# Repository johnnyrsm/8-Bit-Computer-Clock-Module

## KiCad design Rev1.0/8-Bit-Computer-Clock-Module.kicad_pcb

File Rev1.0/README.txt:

//----------------------------------
//      Credits
//----------------------------------

Original Design/Idea by Ben Eater: https://eater.net/

Be sure to check out Ben Eater's home page and youtube channel to check out some more cool stuff.

//----------------------------------
//      General Description
//----------------------------------

Talk about astable, monostable and bistable configs, explain differences and
explain the functionality of the circuit as a whole i.e. generating a continuous clock
or step by step mode using the push button.

Simple PCB layout to practice, made for fun/practice.

Any comments/feedback welcome.

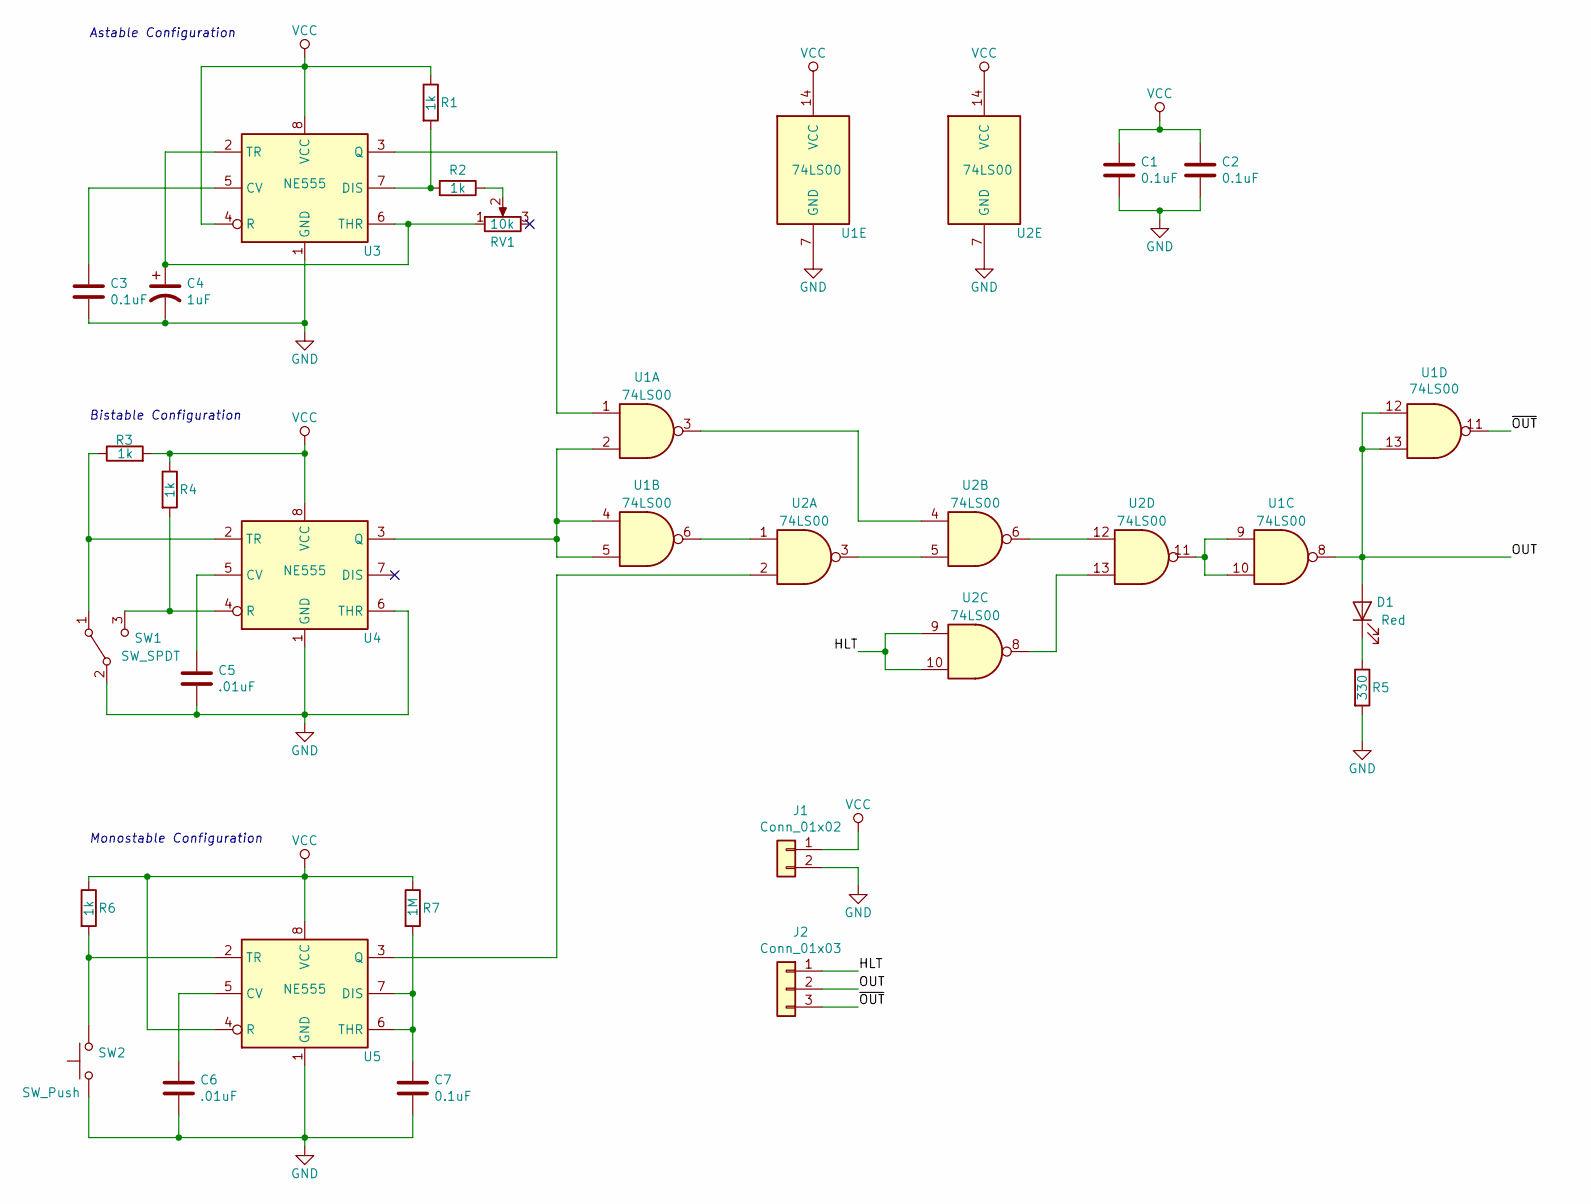
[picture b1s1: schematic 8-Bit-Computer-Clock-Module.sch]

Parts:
C1, C2, C3, C7: 0.1uF; C_Rect_L4.0mm_W2.5mm_P2.50mm
C4: 1uF; CP_Radial_D5.0mm_P2.50mm
C5, C6: .01uF; C_Rect_L4.0mm_W2.5mm_P2.50mm
D1: Red; LED_D3.0mm
J1: Conn_01x02; Pin_Header_Straight_1x02_Pitch2.54mm
J2: Conn_01x03; Pin_Header_Straight_1x03_Pitch2.54mm
R1, R2, R3, R4, R6: 1k; R_Axial_DIN0207_L6.3mm_D2.5mm_P7.62mm_Horizontal
R5: 330; R_Axial_DIN0207_L6.3mm_D2.5mm_P7.62mm_Horizontal
R7: 1M; R_Axial_DIN0207_L6.3mm_D2.5mm_P7.62mm_Horizontal
RV1: 10k; Trimpot_Bourns_3386
SW1: SW_SPDT; Min_Slide_Switch_OS_SPDT
SW2: SW_Push; Sw_Tactile_THT_2_Pin
U1, U2: 74LS00; DIP-14_W7.62mm_Socket
U3, U4, U5: NE555; DIP-8_W7.62mm_Socket

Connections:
/HLT: J2.1, U2.9, U2.10
/OUT: D1.2 (A), J2.2, U1.8, U1.12, U1.13
/~OUT: J2.3, U1.11
GND: C1.2, C2.2, C3.2, C4.2, C5.2, C6.2, C7.2, J1.2, R5.2, SW1.2 (B), SW2.1, U1.7 (GND), U2.7 (GND), U3.1 (GND), U4.1 (GND), U4.6 (THR), U5.1 (GND)
unnamed: C3.1, U3.5 (CV)
unnamed: C4.1, RV1.1, U3.2 (TR), U3.6 (THR)
unnamed: C5.1, U4.5 (CV)
unnamed: C6.1, U5.5 (CV)
unnamed: C7.1, R7.2, U5.6 (THR), U5.7 (DIS)
unnamed: D1.1 (K), R5.1
unnamed: R1.2, R2.2, U3.7 (DIS)
unnamed: R2.1, RV1.2
unnamed: R3.1, SW1.1 (A), U4.2 (TR)
unnamed: R4.2, SW1.3 (C), U4.4 (R)
unnamed: R6.2, SW2.2, U5.2 (TR)
unnamed: U1.1, U3.3 (Q)
unnamed: U1.2, U1.4, U1.5, U4.3 (Q)
unnamed: U1.3, U2.4
unnamed: U1.6, U2.1
unnamed: U1.9, U1.10, U2.11
unnamed: U2.2, U5.3 (Q)
unnamed: U2.3, U2.5
unnamed: U2.6, U2.12
unnamed: U2.8, U2.13
VCC: C1.1, C2.1, J1.1, R1.1, R3.2, R4.1, R6.1, R7.1, U1.14 (VCC), U2.14 (VCC), U3.4 (R), U3.8 (VCC), U4.8 (VCC), U5.4 (R), U5.8 (VCC)

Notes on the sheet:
Astable Configuration
Bistable Configuration
Monostable Configuration

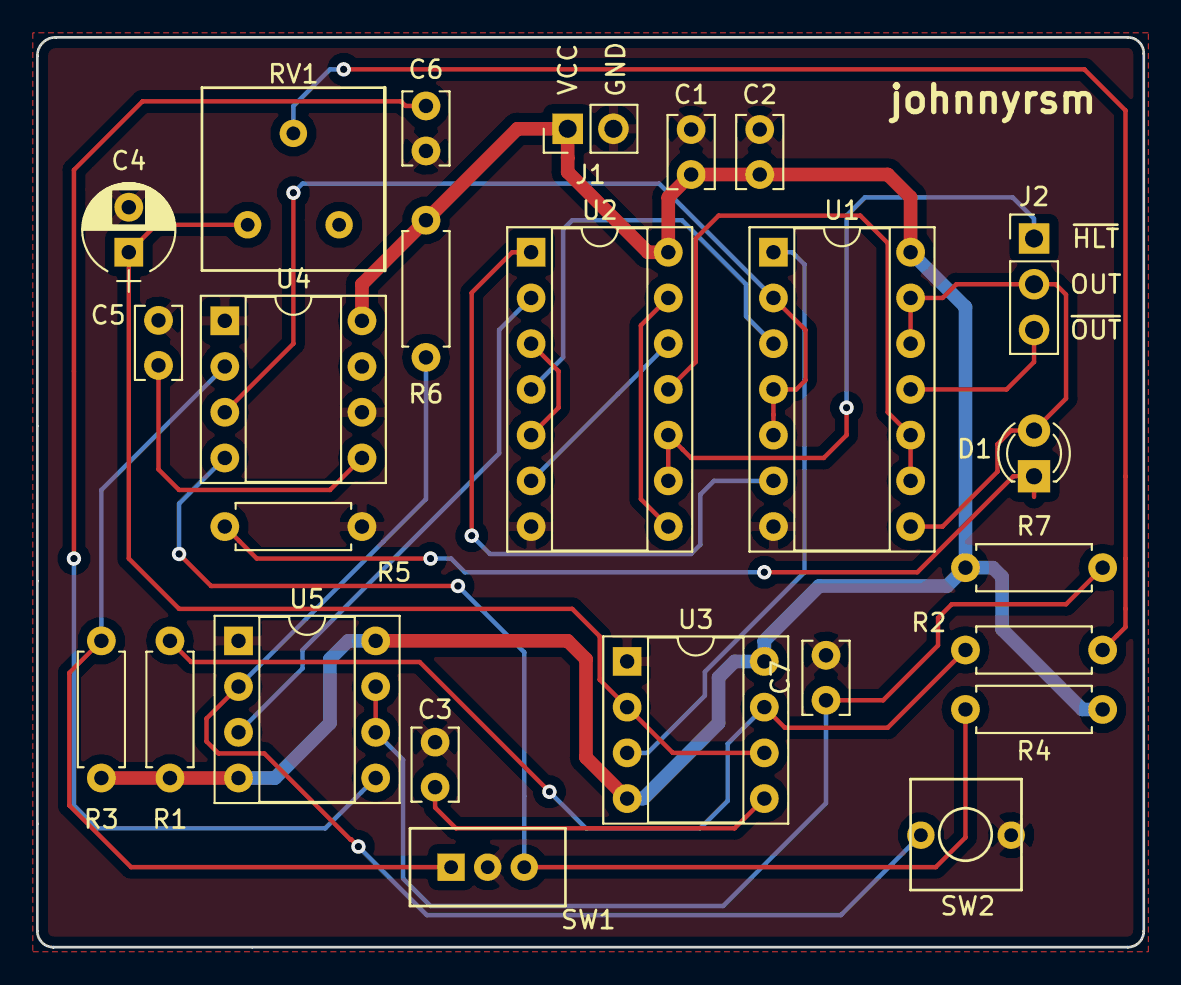
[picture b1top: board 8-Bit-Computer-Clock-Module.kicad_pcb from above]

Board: 2 copper layers, 61.5 x 50.5 mm, 25 parts (0 on the bottom side), 25 nets.

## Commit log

2020-01-11 Initial commit - Kicad Layout Rev1.0
